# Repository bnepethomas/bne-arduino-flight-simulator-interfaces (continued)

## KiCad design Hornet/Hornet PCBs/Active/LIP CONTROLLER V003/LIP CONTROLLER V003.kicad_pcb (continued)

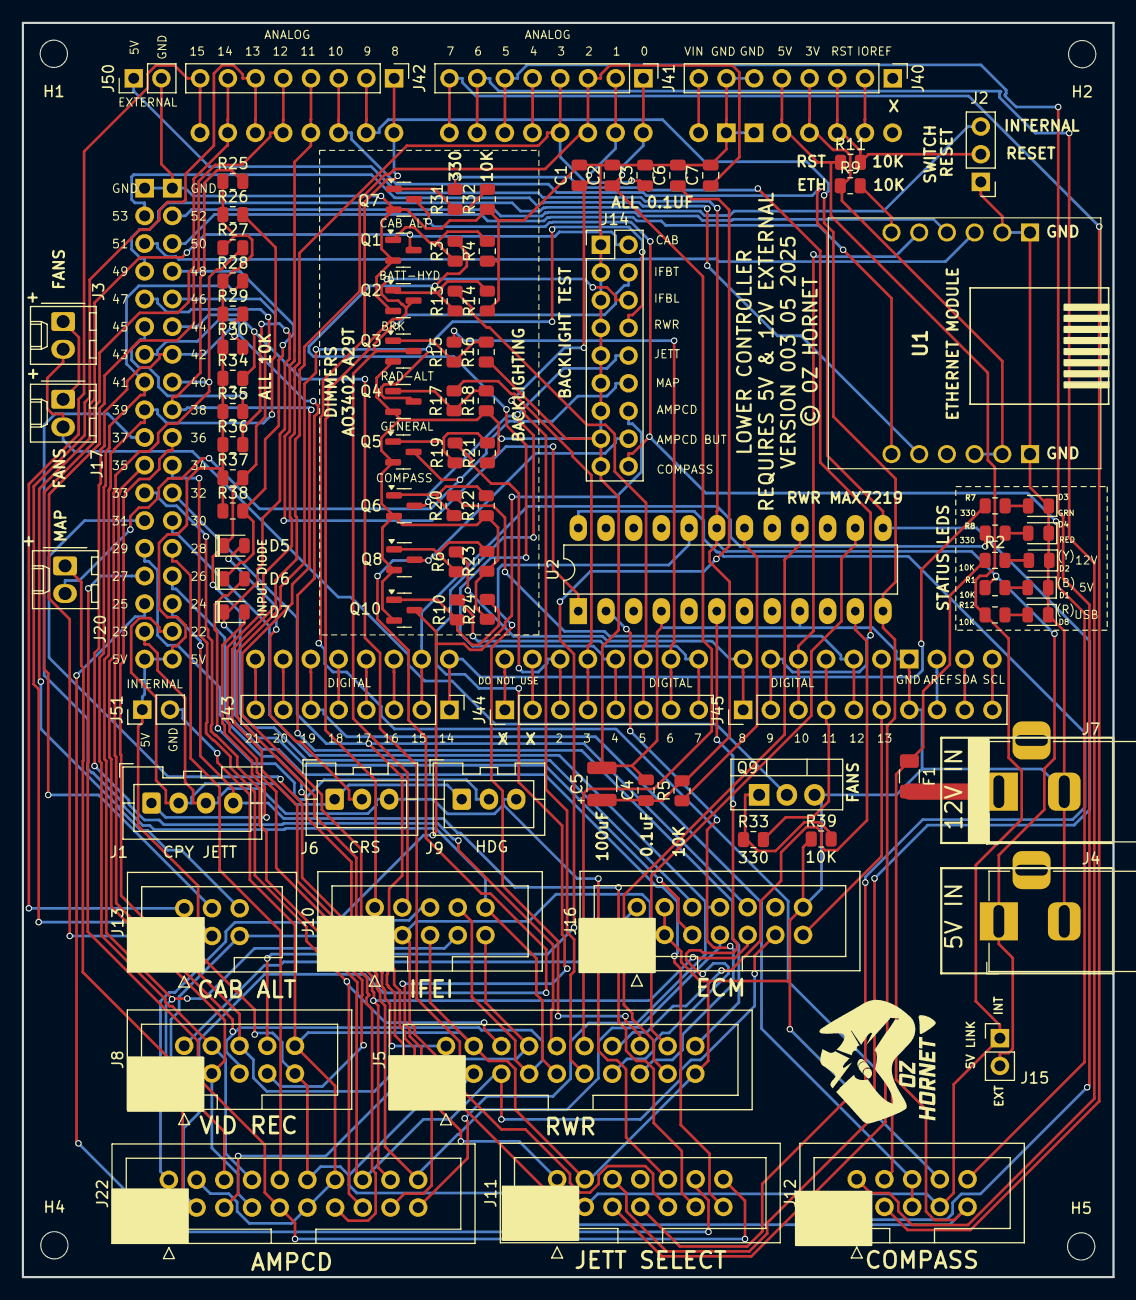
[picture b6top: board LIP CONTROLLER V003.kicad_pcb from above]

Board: 2 copper layers, 100.0 x 115.0 mm, 99 parts (0 on the bottom side), 122 nets.

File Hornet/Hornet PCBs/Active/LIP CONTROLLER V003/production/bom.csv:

Designator,Footprint,Quantity,Value,LCSC Part #
A1,Arduino_Mega2560_R3_Shield,1,Arduino_Mega2560_R3_Shield,
"C1, C2, C3, C4, C6, C7",0805,6,0.1uF,
C5,1210,1,100uF,
"D1, D2, D8",0805,3,LED,
D3,0805,1,GREEN,
D4,0805,1,RED,
"D5, D6, D7",0805,3,D,
F1,1206,1,Polyfuse,
"H1, H5",MountingHole_2.5mm,2,H1,
"H2, H4",MountingHole_2.5mm,2,H2,
J1,JST_XA_B04B-XASK-1_1x04_P2.50mm_Vertical,1,CANOPY_JETT,
J10,IDC-Header_2x05_P2.54mm_Vertical,1,IFEI,
J11,IDC-Header_2x07_P2.54mm_Vertical,1,JETT,
J12,IDC-Header_2x05_P2.54mm_Vertical,1,COMPASS,
J13,IDC-Header_2x03_P2.54mm_Vertical,1,CABIN_ALT,
J14,PinHeader_2x09_P2.54mm_Vertical,1,Conn_02x09_Odd_Even,
"J15, J50, J51",PinHeader_1x02_P2.54mm_Vertical,3,Conn_01x02,
J16,IDC-Header_2x07_P2.54mm_Vertical,1,EMC_JETT,
"J17, J3",Molex_KK-254_AE-6410-02A_1x02_P2.54mm_Vertical,2,FANS,
J2,PinHeader_1x03_P2.54mm_Vertical,1,Conn_01x03_Pin,
J20,Molex_KK-254_AE-6410-02A_1x02_P2.54mm_Vertical,1,MAP,
J22,IDC-Header_2x10_P2.54mm_Vertical,1,AMPCD,
J4,BarrelJack_Horizontal,1,5V IN,
"J40, J41, J42, J43, J44",PinHeader_1x08_P2.54mm_Vertical,5,Conn_01x08,
J45,PinHeader_1x10_P2.54mm_Vertical,1,Conn_01x10,
J5,IDC-Header_2x10_P2.54mm_Vertical,1,RWR,
J6,JST_XA_B03B-XASK-1_1x03_P2.50mm_Vertical,1,CRS,
J7,BarrelJack_Horizontal,1,STEPPER IN 12-20VDC,
J8,IDC-Header_2x05_P2.54mm_Vertical,1,VID_REC,
J9,JST_XA_B03B-XASK-1_1x03_P2.50mm_Vertical,1,HDG,
"Q1, Q10, Q2, Q3, Q4, Q5, Q6, Q7, Q8",SOT-23,9,Q_NMOS_GSD,
Q9,TO-220-3_Vertical,1,IRF1405PBF,
"R1, R12",0805,2,5K,
"R10, R13, R15, R17, R19, R20, R3, R31, R33, R6, R7, R8",0805,12,330,
"R11, R14, R16, R18, R2, R21, R22, R23, R24, R25, R26, R27, R28, R29, R30, R32, R34, R35, R36, R37, R38, R39, R4, R5, R9",0805,25,10K,
U1,USRES1,1,USR-ES1,
U2,DIP-24_W7.62mm_LongPads,1,MAX7219,

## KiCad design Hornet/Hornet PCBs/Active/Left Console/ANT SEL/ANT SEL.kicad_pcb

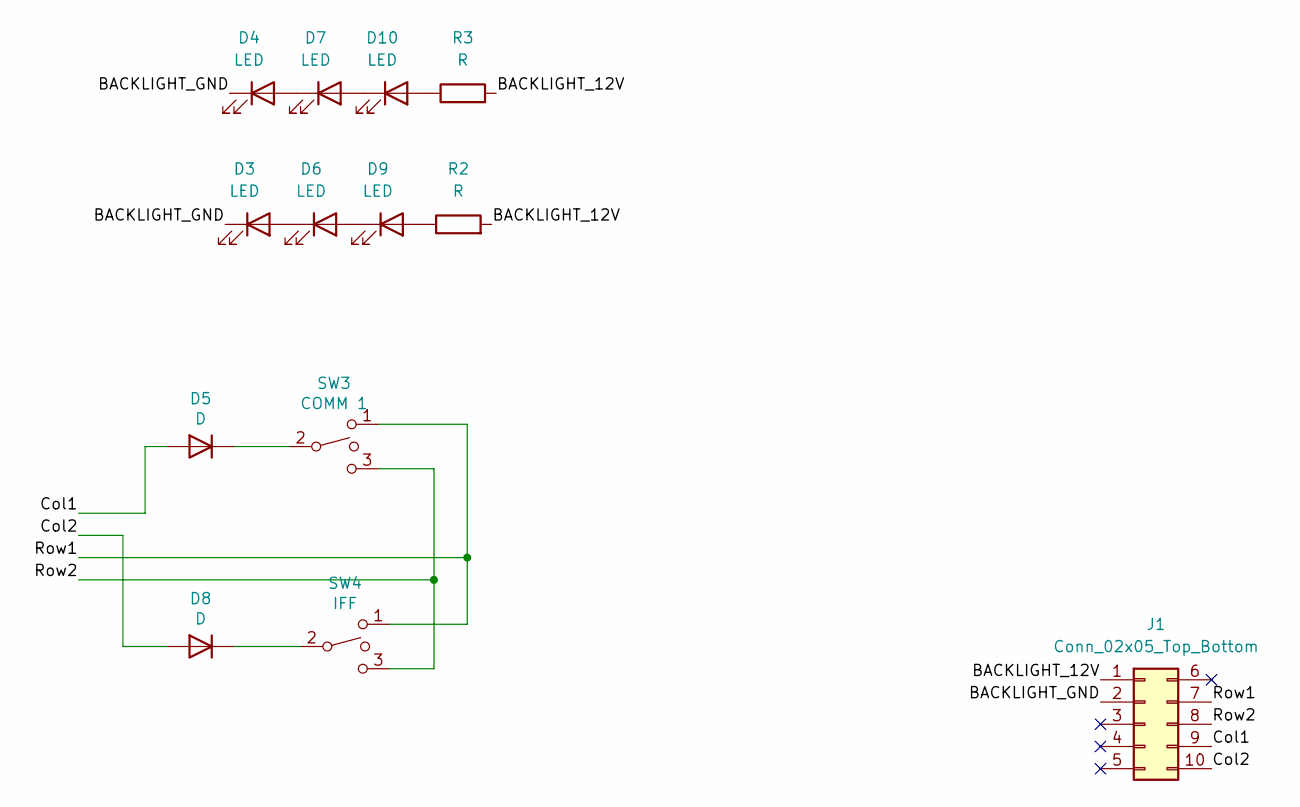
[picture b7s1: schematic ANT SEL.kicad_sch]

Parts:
D3, D4, D6, D7, D9, D10: LED; LED_D3.0mm_FlatTop
D5, D8: D; D_DO-35_SOD27_P7.62mm_Horizontal
J1: Conn_02x05_Top_Bottom; IDC-Header_2x05_P2.54mm_Vertical
R2, R3: R; R_Axial_DIN0204_L3.6mm_D1.6mm_P7.62mm_Horizontal
SW3: COMM 1; Molex_KK-254_AE-6410-03A_1x03_P2.54mm_Vertical
SW4: IFF; Molex_KK-254_AE-6410-03A_1x03_P2.54mm_Vertical

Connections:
/BACKLIGHT_12V: J1.1, R2.2, R3.2
/BACKLIGHT_GND: D3.1 (K), D4.1 (K), J1.2
/Col1: D5.2 (A), J1.9
/Col2: D8.2 (A), J1.10
/Row1: J1.7, SW3.1, SW4.1
/Row2: J1.8, SW3.3, SW4.3
unnamed: D3.2 (A), D6.1 (K)
unnamed: D4.2 (A), D7.1 (K)
unnamed: D5.1 (K), SW3.2
unnamed: D6.2 (A), D9.1 (K)
unnamed: D8.1 (K), SW4.2
unnamed: D9.2 (A), R2.1
unnamed: D10.2 (A), R3.1
unnamed: D7.2 (A), D10.1 (K)

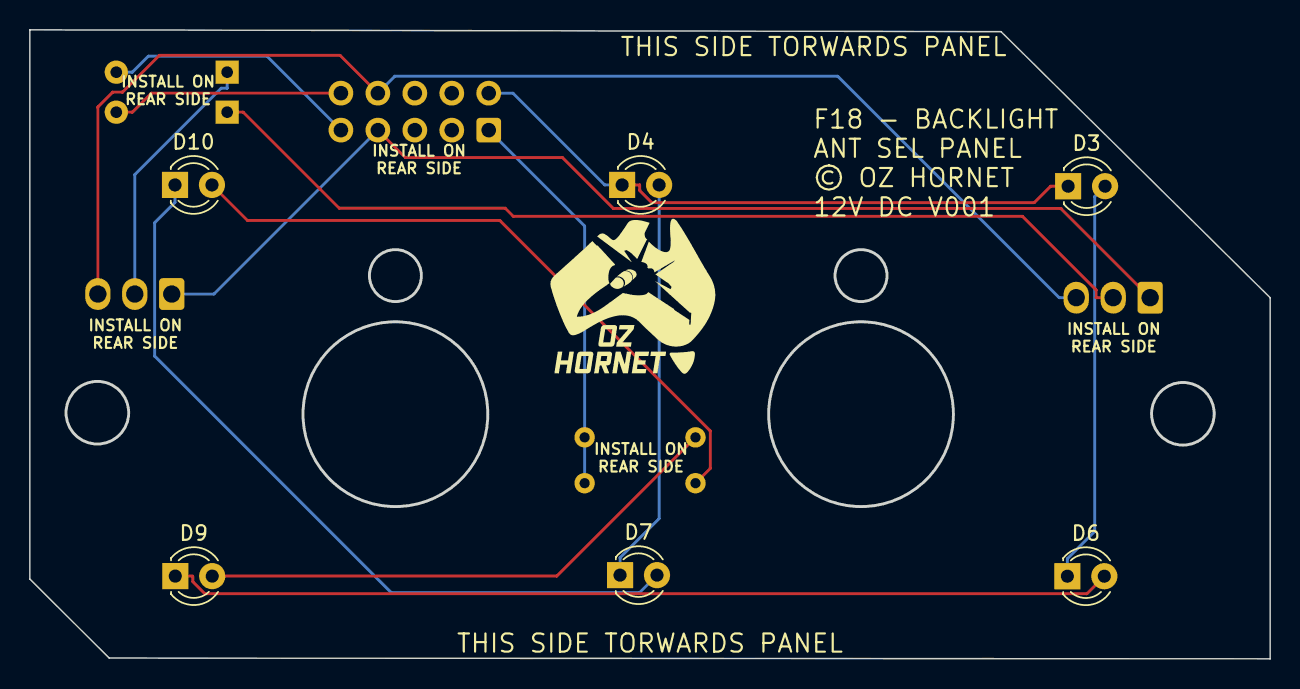
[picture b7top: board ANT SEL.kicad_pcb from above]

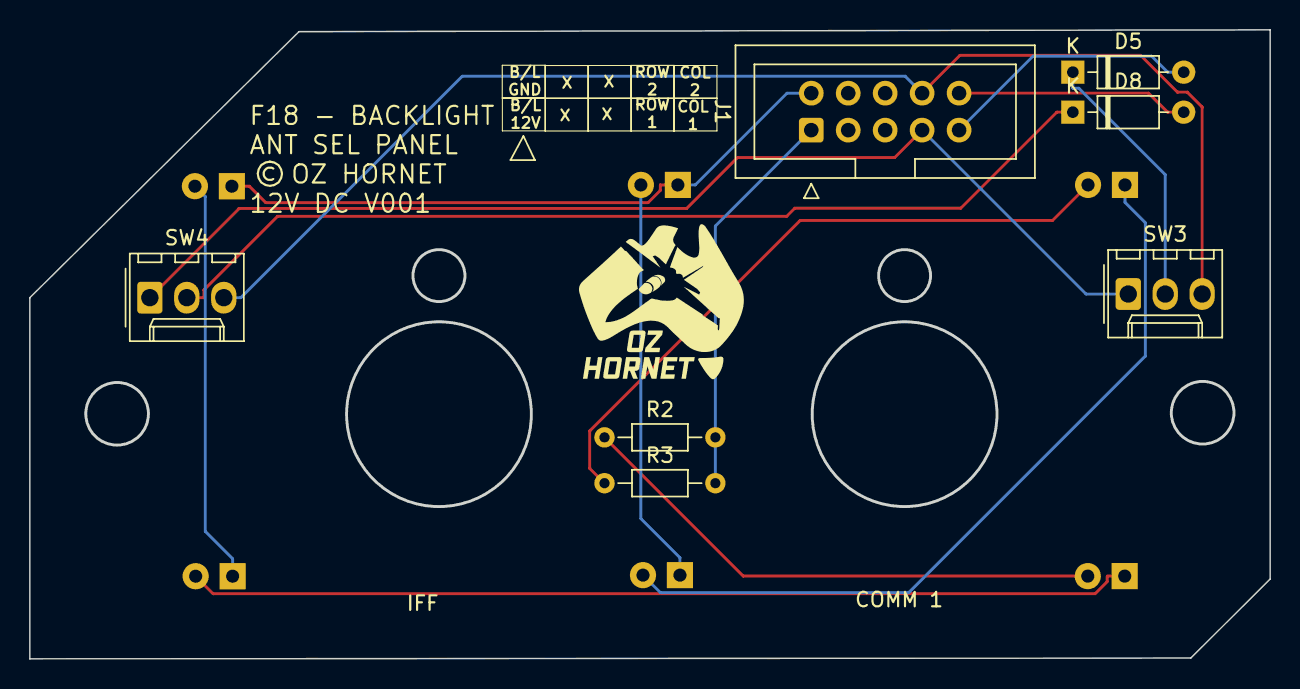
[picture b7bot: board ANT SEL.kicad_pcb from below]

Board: 2 copper layers, 85.3 x 43.2 mm, 13 parts (7 on the bottom side), 14 nets.

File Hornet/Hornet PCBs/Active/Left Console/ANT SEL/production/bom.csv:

Designator,Footprint,Quantity,Value,LCSC Part #
"D10, D3, D4, D6, D7, D9",LED_D3.0mm_FlatTop,6,LED,
"D5, D8",D_DO-35_SOD27_P7.62mm_Horizontal,2,D,
J1,IDC-Header_2x05_P2.54mm_Vertical,1,Conn_02x05_Top_Bottom,
"R2, R3",R_Axial_DIN0204_L3.6mm_D1.6mm_P7.62mm_Horizontal,2,R,
SW3,Molex_KK-254_AE-6410-03A_1x03_P2.54mm_Vertical,1,COMM 1,
SW4,Molex_KK-254_AE-6410-03A_1x03_P2.54mm_Vertical,1,IFF,
